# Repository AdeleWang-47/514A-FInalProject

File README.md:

# 514A-FInalProject
## Section 1

A system to provide safe, low-brightness lighting when users get out of bed at night. 
One sensing device shaped like a carpet and one displaying device can be place at the corner of the room to light the path for user.

## Section 2

## Section 3

## Section 4

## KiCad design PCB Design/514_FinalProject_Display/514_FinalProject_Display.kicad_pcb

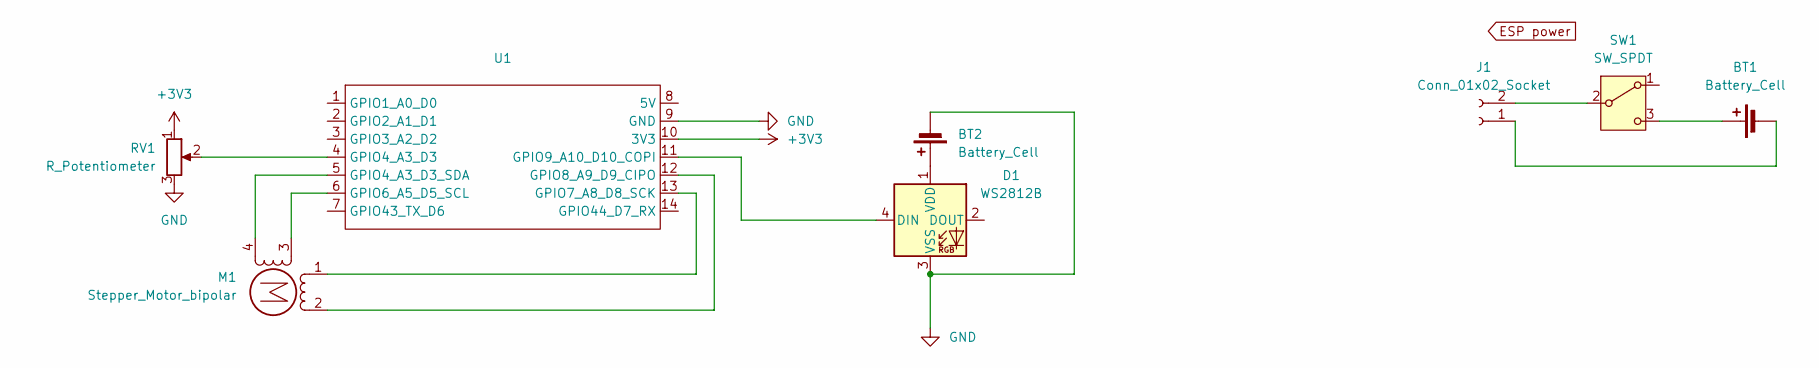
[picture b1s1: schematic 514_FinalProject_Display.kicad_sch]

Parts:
BT1: Battery_Cell; BatteryHolder_Keystone_1042_1x18650
BT2: Battery_Cell; BarrelJack_Kycon_KLDX-0202-xC_Horizontal
D1: WS2812B; PinHeader_1x04_P2.54mm_Vertical
J1: Conn_01x02_Socket; PinHeader_1x02_P2.54mm_Vertical
M1: Stepper_Motor_bipolar; x27_stepper
RV1: R_Potentiometer; PinHeader_1x03_P2.54mm_Horizontal
SW1: SW_SPDT; PinHeader_1x03_P2.54mm_Vertical
U1: XIAO_ESP32_SENSE

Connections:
+3V3: RV1.1, U1.10 (3V3)
GND: BT2.2 (-), D1.3 (VSS), RV1.3, U1.9 (GND)
unnamed: BT1.1 (+), SW1.3 (C)
unnamed: BT1.2 (-), J1.1
unnamed: BT2.1 (+), D1.1 (VDD)
unnamed: D1.4 (DIN), U1.11 (GPIO9_A10_D10_COPI)
unnamed: J1.2, SW1.2 (B)
unnamed: M1.2 (-), U1.12 (GPIO8_A9_D9_CIPO)
unnamed: RV1.2, U1.4 (GPIO4_A3_D3)
unnamed: M1.4, U1.5 (GPIO4_A3_D3_SDA)
unnamed: M1.3, U1.6 (GPIO6_A5_D5_SCL)
unnamed: M1.1, U1.13 (GPIO7_A8_D8_SCK)

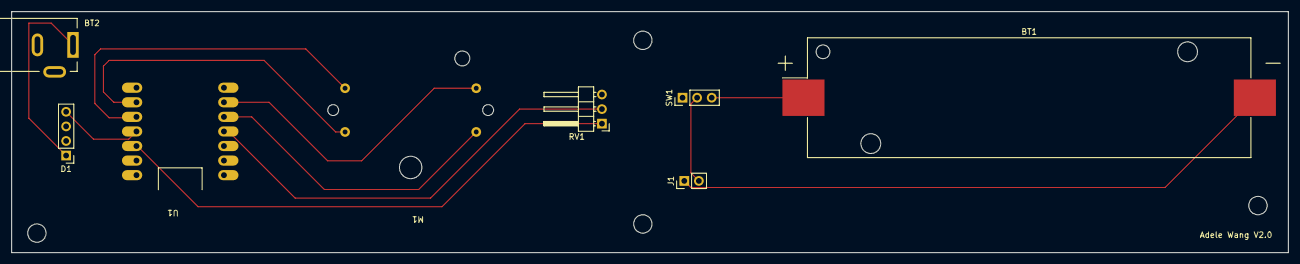
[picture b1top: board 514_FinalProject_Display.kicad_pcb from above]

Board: 2 copper layers, 222.5 x 42.0 mm, 8 parts (0 on the bottom side), 12 nets.

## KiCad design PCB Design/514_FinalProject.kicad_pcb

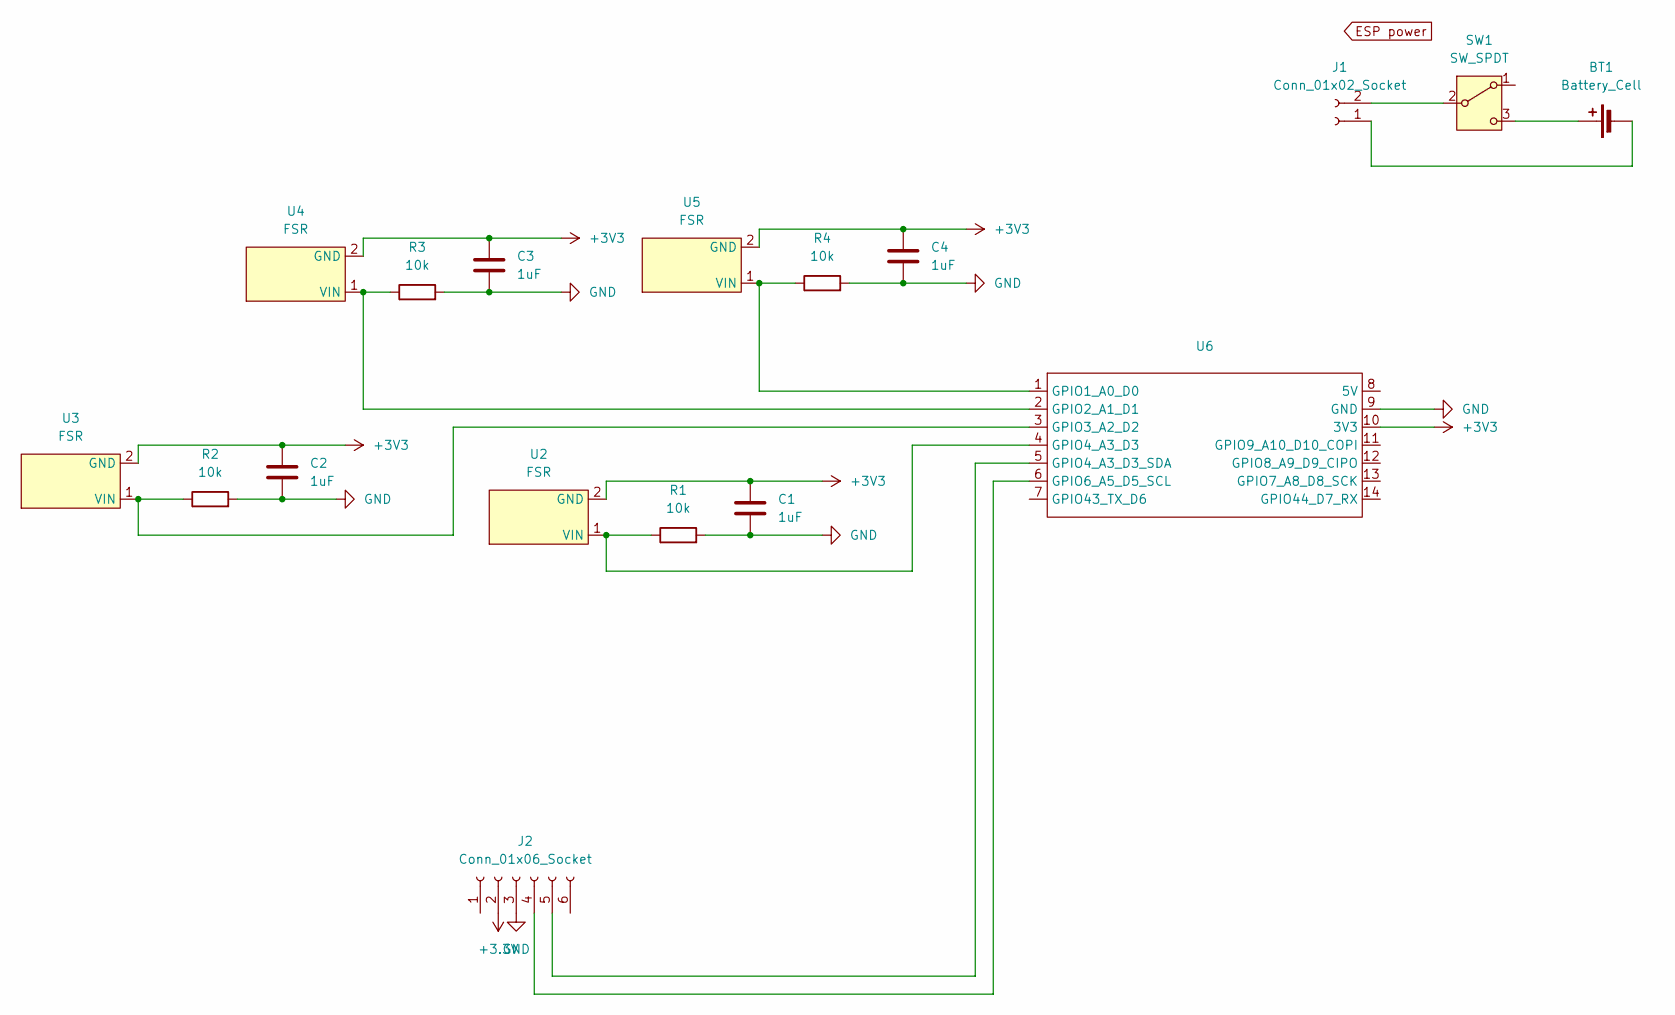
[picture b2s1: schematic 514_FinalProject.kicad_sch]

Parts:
BT1: Battery_Cell; BatteryHolder_Keystone_1042_1x18650
C1, C2, C3, C4: 1uF; C_0805_2012Metric_Pad1.18x1.45mm_HandSolder
J1: Conn_01x02_Socket; PinHeader_1x02_P2.54mm_Vertical
J2: Conn_01x06_Socket; PinHeader_1x05_P2.54mm_Vertical
R1, R2, R3, R4: 10k; R_0805_2012Metric_Pad1.20x1.40mm_HandSolder
SW1: SW_SPDT; PinHeader_1x03_P2.54mm_Vertical
U2, U3, U4, U5: FSR; PinHeader_1x02_P2.54mm_Vertical
U6: XIAO_ESP32_SENSE

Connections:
+3.3V: J2.2
+3V3: C1.1, C2.1, C3.1, C4.1, U2.2 (GND), U3.2 (GND), U4.2 (GND), U5.2 (GND), U6.10 (3V3)
GND: C1.2, C2.2, C3.2, C4.2, J2.3, R1.2, R2.2, R3.2, R4.2, U6.9 (GND)
unnamed: BT1.1 (+), SW1.3 (C)
unnamed: BT1.2 (-), J1.1
unnamed: J1.2, SW1.2 (B)
unnamed: J2.4, U6.6 (GPIO6_A5_D5_SCL)
unnamed: J2.5, U6.5 (GPIO4_A3_D3_SDA)
unnamed: R1.1, U2.1 (VIN), U6.4 (GPIO4_A3_D3)
unnamed: R2.1, U3.1 (VIN), U6.3 (GPIO3_A2_D2)
unnamed: R3.1, U4.1 (VIN), U6.2 (GPIO2_A1_D1)
unnamed: R4.1, U5.1 (VIN), U6.1 (GPIO1_A0_D0)

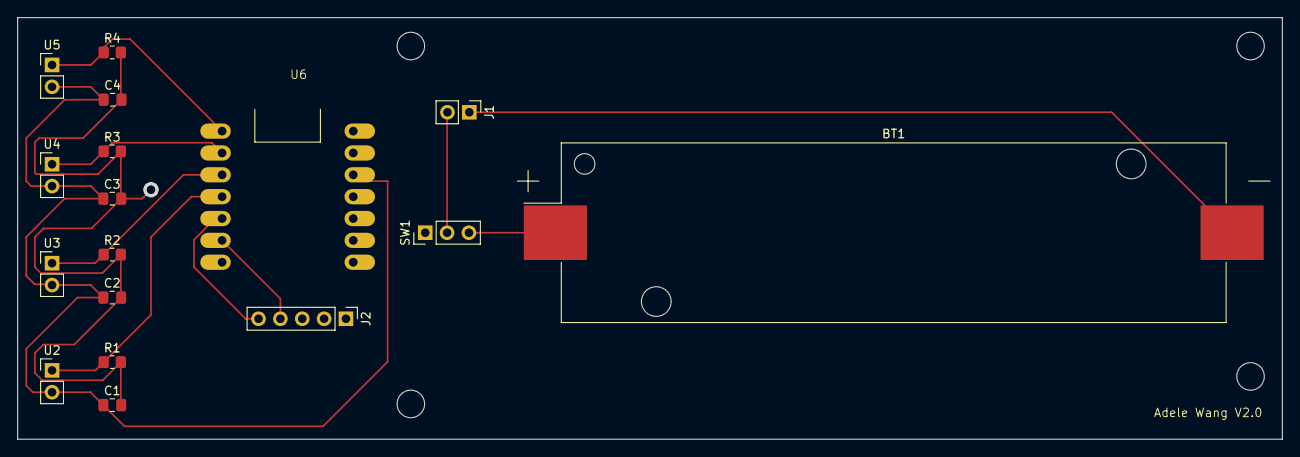
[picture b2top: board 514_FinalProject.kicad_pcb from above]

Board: 2 copper layers, 147.0 x 49.0 mm, 17 parts (0 on the bottom side), 11 nets.

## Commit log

2025-01-23 second commit
2025-01-23 Third commit
2025-01-29 PCB Design Progress
2025-02-14 Battery Life Estimate
2025-03-11 codes
